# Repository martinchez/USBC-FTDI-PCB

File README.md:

# USB-C FTDI Breakout Board Design

This repository contains the design files for a USB-C FTDI breakout board created using KiCad. This breakout board is designed to convert USB signals to serial communication, making it useful for programming, debugging, and interfacing with microcontrollers and other serial devices.

## Project Overview

This project includes:
- **Schematic Design**: Circuitry for FTDI (USB-to-Serial) chip with USB-C connector.
- **PCB Layout**: Compact PCB design for easy connection to serial devices.
- **Production Files**: Gerber files and a BOM (Bill of Materials) for manufacturing.

## Features

- **USB-C Connector**: Modern USB-C connection for compatibility with most modern devices.
- **FTDI Chip**: USB-to-Serial conversion for programming and debugging.
- **Breakout Pins**: Exposed TX, RX, VCC, and GND pins for easy connection.
- **Voltage Selection**: Supports 3.3V and 5V operation via a jumper or switch.

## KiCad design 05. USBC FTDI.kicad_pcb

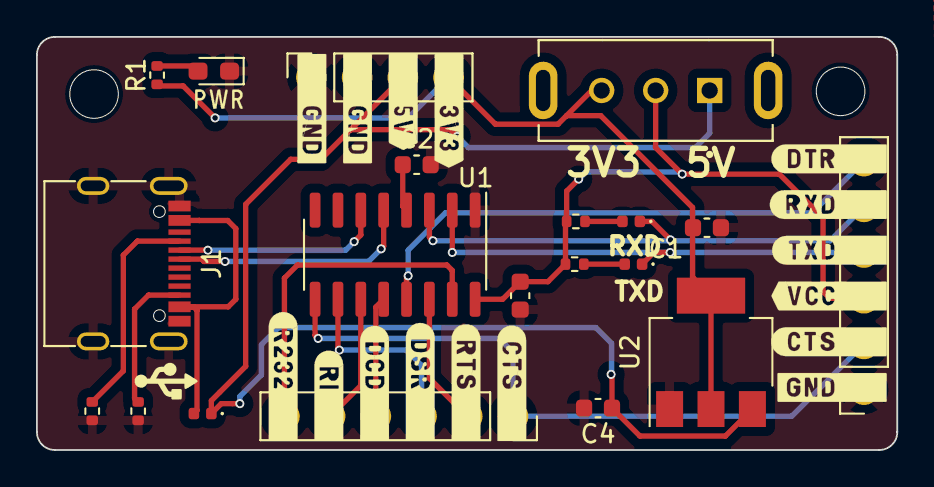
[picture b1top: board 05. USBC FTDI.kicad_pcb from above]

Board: 2 copper layers, 47.8 x 23.0 mm, 22 parts (0 on the bottom side), 22 nets.

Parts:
C1, C4: 2.2uF; C_0603_1608Metric
C2, C3: 100n; C_0603_1608Metric
D1: Purple; LED_0603_1608Metric_Pad1.05x0.95mm_HandSolder
D2: WHITE; LED_0402_1005Metric
D3: BLUE; LED_0402_1005Metric
F1: Fuse; LED_0402_1005Metric
H1, H2: MountingHole; MountingHole_2.7mm_M2.5
J1: USB_C_Receptacle_USB2.0; USB_C_Receptacle_G-Switch_GT-USB-7010ASV
J2, J3: Conn_01x06_Pin; PinSocket_1x06_P2.54mm_Vertical
J4: Conn_01x04_Pin; PinSocket_1x04_P2.54mm_Vertical
R1: 2K2; R_0402_1005Metric
R2, R3: 10k; R_0402_1005Metric
R4, R5: 5k1; R_0402_1005Metric
S1: EG1206; SW_EG1206
U1: CH340C; SOIC-16_3.9x9.9mm_P1.27mm
U2: AMS1117-3.3; SOT-223-3_TabPin2

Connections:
+3V3: C1.1, J4.4, R1.1, S1.3, U2.2 (VO)
CTS: J2.1, J3.2, U1.9 (~CTS)
D+: J1.A6 (D+), J1.B6 (D+), U1.5 (UD+)
D-: J1.A7 (D-), J1.B7 (D-), U1.6 (UD-)
DCD: J2.4, U1.12 (~DCD)
DSR: J2.3, U1.10 (~DSR)
DTR: J3.6, U1.13 (~DTR)
GND: C1.2, C2.2, C3.2, C4.2, D1.1 (K), J1.A1 (GND), J1.A12 (GND), J1.B1 (GND), J1.B12 (GND), J1.S1 (SHIELD), J3.1, J4.1, J4.2, R4.1, R5.1, U1.1 (GND), U2.1 (GND)
unnamed: D1.2 (A), R1.2
unnamed: D2.2 (A), R2.2
unnamed: D3.2 (A), R3.2
unnamed: F1.2, J1.A4 (VBUS), J1.A9 (VBUS), J1.B4 (VBUS), J1.B9 (VBUS)
unnamed: J1.A5 (CC1), R4.2
unnamed: J1.B5 (CC2), R5.2
unnamed: C2.1, U1.4 (V3)
R232: J2.6, U1.15 (R232)
RI: J2.5, U1.11 (~RI)
RTS: J2.2, U1.14 (~RTS)
RXD0: D3.1 (K), J3.5, U1.3 (RXD)
TXD0: D2.1 (K), J3.4, U1.2 (TXD)
VCC_OUT: C3.1, J3.3, R2.1, R3.1, S1.2, U1.16 (VCC)
VUSB: C4.1, F1.1, J4.3, S1.1, U2.3 (VI)

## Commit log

2024-11-11 readme
